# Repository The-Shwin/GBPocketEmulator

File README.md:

# GBPocketEmulator

## Summary
In my spare time, I am designing a circuit board that will fit in a Gameboy Pocket shell. It will control the buttons and be used for interfacing a display and Raspberry Pi Zero W. This is a work in progress.

### Components
* Display: Adafruit 2.2" 18-bit color TFT LCD display with microSD card breakout 
  * https://www.adafruit.com/product/1480#technical-details
* Raspberry Pi Zero W
* Game Boy Pocket housing and buttons (from Retro Game Repair Shop)

There are still a more components to be sourced/selected. The major remaining component to be selected is the battery.

### The PCB
The PCB was planned to fit into the Gameboy Pocket housing. This poses a fun challenge as space becomes a constraint. The current plan is to use one large PCB that will have conductive pads for original Gameboy Pocket style buttons. It will also connect the speaker, 3.5mm audio jack, the 2.2" TFT display, and the Raspberry Pi Zero W's 40-pin header. The display and buttons would be connected via the front side of the board, while the remaining components would be connected via the back. 

### Emulator
The current plan for the software is to run RetroPie on the Raspberry Pi Zero W. This will allow for emulation of a fair variety of games and old retro consoles.

### Open Sourcing
I don't have any intention of profitting off of this project. It is just for fun. Therefore, please feel free to improve or modify the designs. I'd appreciate it if you let me know or fork the repository, just so I can know if this project is actually helping other people with their designs. Please don't try to sell this yourself.

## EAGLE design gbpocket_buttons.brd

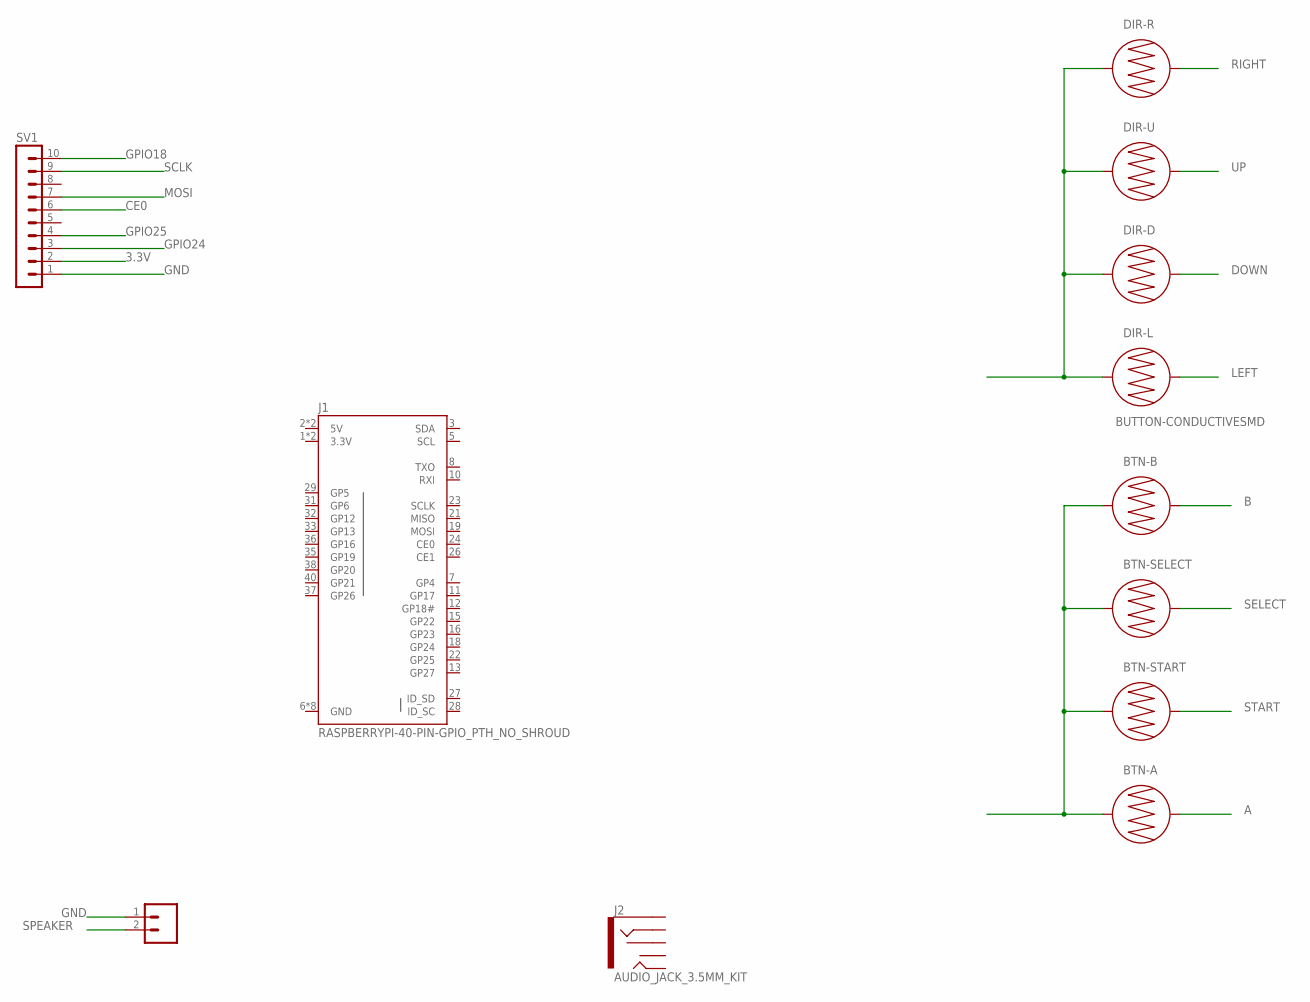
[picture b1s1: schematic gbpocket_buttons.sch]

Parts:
BTN-A: BUTTON-CONDUCTIVESMD; BUTTON-CONDUCTIVE
BTN-B: BUTTON-CONDUCTIVESMD; BUTTON-CONDUCTIVE
BTN-SELECT: BUTTON-CONDUCTIVESMD; BUTTON-CONDUCTIVE
BTN-START: BUTTON-CONDUCTIVESMD; BUTTON-CONDUCTIVE
DIR-D: BUTTON-CONDUCTIVESMD; BUTTON-CONDUCTIVE
DIR-L: BUTTON-CONDUCTIVESMD; BUTTON-CONDUCTIVE
DIR-R: BUTTON-CONDUCTIVESMD; BUTTON-CONDUCTIVE
DIR-U: BUTTON-CONDUCTIVESMD; BUTTON-CONDUCTIVE
J1: RASPBERRYPI-40-PIN-GPIO_PTH_NO_SHROUD; 2X20
J2: AUDIO_JACK_3.5MM_KIT; AUDIO-JACK-KIT
JP2: M02PTH; 1X02
SV1: MA10-1

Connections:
3.3V: J1.1 (3.3V), J1.17 (3.3V), SV1.2
5V: J1.2 (5V), J1.4 (5V)
A: BTN-A.2
B: BTN-B.2
CE0: SV1.6
DOWN: DIR-D.2
GND: BTN-A.1, BTN-B.1, BTN-SELECT.1, BTN-START.1, DIR-D.1, DIR-L.1, DIR-R.1, DIR-U.1, J1.6 (GND), J1.9 (GND), J1.14 (GND), J1.20 (GND), J1.25 (GND), J1.30 (GND), J1.34 (GND), J1.39 (GND), JP2.1, SV1.1
GPIO18: SV1.10
GPIO24: SV1.3
GPIO25: SV1.4
LEFT: DIR-L.2
MOSI: SV1.7
RIGHT: DIR-R.2
SCLK: SV1.9
SELECT: BTN-SELECT.2
SPEAKER: JP2.2
START: BTN-START.2
UP: DIR-U.2

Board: 2 copper layers, 24 parts (0 on the bottom side), 3 nets, no tracks yet.

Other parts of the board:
U$1, U$2, U$3, U$4, U$5, U$6, U$7, U$8, U$9, U$10, U$11, U$12: STAND-OFF

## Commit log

2020-05-04 Adding board and schematic that I have so far.
2020-05-04 Updated to board and snapshot of progress
2020-05-04 Create gbpocket_buttons.b##

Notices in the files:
parts and their libraries:
SparkFun-Connectors: Licensing: CC v3.0 Share-Alike You are welcome to use this library for commercial purposes.
SparkFun-Switches: Licensing: Creative Commons ShareAlike 4.0 International - https://creativecommons.org/licenses/by-sa/4.0
